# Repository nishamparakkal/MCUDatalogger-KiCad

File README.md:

# MCU Datalogger

## Overview

A microcontroller-based data logger designed in KiCad.

The design uses an ATmega328P microcontroller, DS1337 real-time clock, and external EEPROM memory for time-stamped data storage.

## Features

- ATmega328P-AU microcontroller
- DS1337 Real-Time Clock (RTC)
- Dual 24LC1025 EEPROM memory chips
- External crystal oscillators
- Status indicator LEDs
- I2C communication bus
- Expansion pin headers
- Two-layer PCB design
- ERC and DRC verified
- Manufacturing-ready Gerber files

## Tools Used
- KiCad 10
- Git

## Schematic

## PCB Layout

## 3D View

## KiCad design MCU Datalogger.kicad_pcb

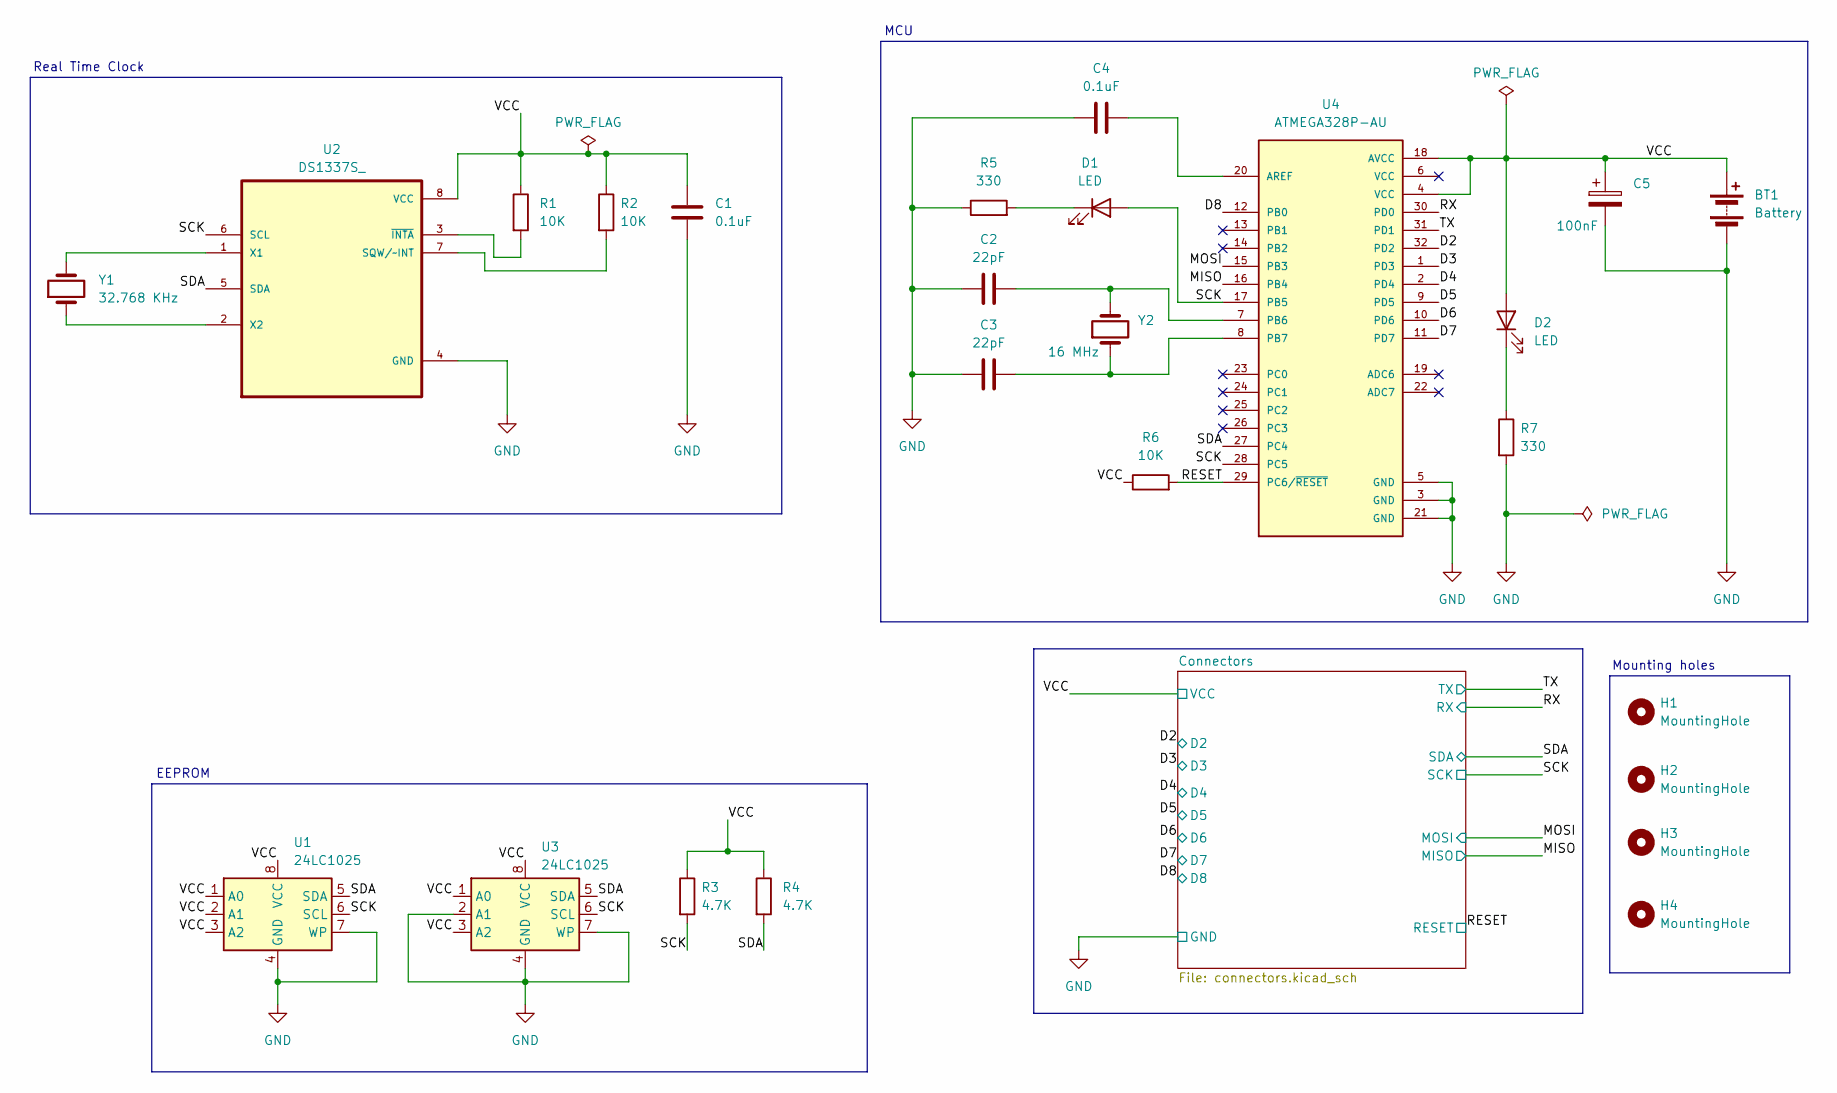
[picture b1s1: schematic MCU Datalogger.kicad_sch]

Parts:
BT1: Battery; PinHeader_1x02_P2.54mm_Vertical
C1, C4: 0.1uF; C_0805_2012Metric
C2, C3: 22pF; C_0805_2012Metric
C5: 100nF; C_0805_2012Metric
D1, D2: LED; LED_0805_2012Metric
H1, H2, H3, H4: MountingHole; MountingHole_2.1mm
R1, R2, R6: 10K; R_0805_2012Metric
R3, R4: 4.7K; R_0805_2012Metric
R5, R7: 330; R_0805_2012Metric
U1, U3: 24LC1025; SOIC-8_5.3x5.3mm_P1.27mm
U2: DS1337S_; SOIC127P600X175-8N
U4: ATMEGA328P-AU; QFP80P900X900X120-32N; PARTREV 8271A
Y1: 32.768 KHz; Crystal_SMD_5032-2Pin_5.0x3.2mm_HandSoldering
Y2: 16 MHz; Crystal_SMD_5032-2Pin_5.0x3.2mm_HandSoldering

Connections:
/D2: U4.32 (PD2); also elsewhere on the board
/D3: U4.1 (PD3); also elsewhere on the board
/D4: U4.2 (PD4); also elsewhere on the board
/D5: U4.9 (PD5); also elsewhere on the board
/D6: U4.10 (PD6); also elsewhere on the board
/D7: U4.11 (PD7); also elsewhere on the board
/D8: U4.12 (PB0); also elsewhere on the board
/MISO: U4.16 (PB4); also elsewhere on the board
/MOSI: U4.15 (PB3); also elsewhere on the board
/RESET: R6.2, U4.29 (PC6/~RESET); also elsewhere on the board
/RX: U4.30 (PD0); also elsewhere on the board
/SCK: D1.2 (A), R3.2, U1.6 (SCL), U2.6 (SCL), U3.6 (SCL), U4.17 (PB5), U4.28 (PC5); also elsewhere on the board
/SDA: R4.2, U1.5 (SDA), U2.5 (SDA), U3.5 (SDA), U4.27 (PC4); also elsewhere on the board
/TX: U4.31 (PD1); also elsewhere on the board
/VCC: BT1.1 (+), C1.1, C5.1, D2.2 (A), R1.1, R2.1, R3.1, R4.1, R6.1, U1.1 (A0), U1.2 (A1), U1.3 (A2), U1.8 (VCC), U2.8 (VCC), U3.1 (A0), U3.3 (A2), U3.8 (VCC), U4.4 (VCC), U4.18 (AVCC); also elsewhere on the board
GND: BT1.2 (-), C1.2, C2.2, C3.1, C4.1, C5.2, R5.1, R7.2, U1.4 (GND), U1.7 (WP), U2.4 (GND), U3.2 (A1), U3.4 (GND), U3.7 (WP), U4.3 (GND), U4.5 (GND), U4.21 (GND); also elsewhere on the board
unnamed: D1.1 (K), R5.2
unnamed: D2.1 (K), R7.1
unnamed: R2.2, U2.7 (SQW/~INT)
unnamed: U2.1 (X1), Y1.2
unnamed: U2.2 (X2), Y1.1
unnamed: R1.2, U2.3 (~INTA)
unnamed: C4.2, U4.20 (AREF)
unnamed: C2.1, U4.7 (PB6), Y2.2
unnamed: C3.2, U4.8 (PB7), Y2.1

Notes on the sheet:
EEPROM
MCU
Real Time Clock
Mounting holes

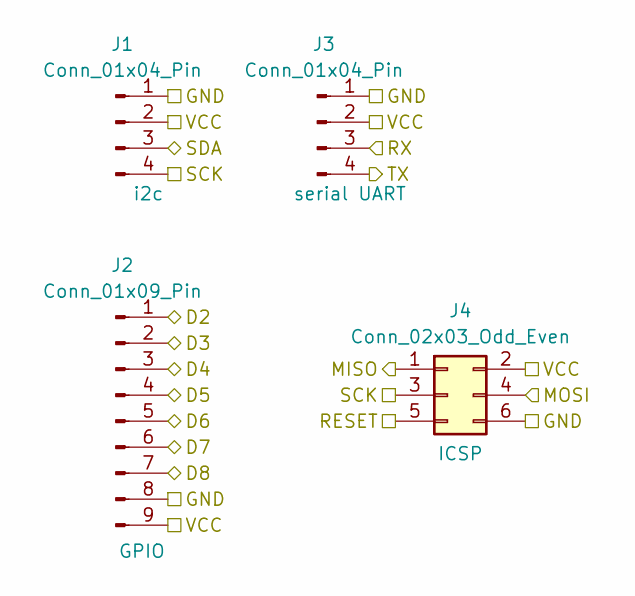
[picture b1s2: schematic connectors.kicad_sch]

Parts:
J1, J3: Conn_01x04_Pin; PinHeader_1x04_P2.54mm_Vertical
J2: Conn_01x09_Pin; PinHeader_1x09_P2.54mm_Vertical
J4: Conn_02x03_Odd_Even; PinHeader_2x03_P2.54mm_Vertical

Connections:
/D2: J2.1; also elsewhere on the board
/D3: J2.2; also elsewhere on the board
/D4: J2.3; also elsewhere on the board
/D5: J2.4; also elsewhere on the board
/D6: J2.5; also elsewhere on the board
/D7: J2.6; also elsewhere on the board
/D8: J2.7; also elsewhere on the board
/MISO: J4.1; also elsewhere on the board
/MOSI: J4.4; also elsewhere on the board
/RESET: J4.5; also elsewhere on the board
/RX: J3.3; also elsewhere on the board
/SCK: J1.4, J4.3; also elsewhere on the board
/SDA: J1.3; also elsewhere on the board
/TX: J3.4; also elsewhere on the board
/VCC: J1.2, J2.9, J3.2, J4.2; also elsewhere on the board
GND: J1.1, J2.8, J3.1, J4.6; also elsewhere on the board

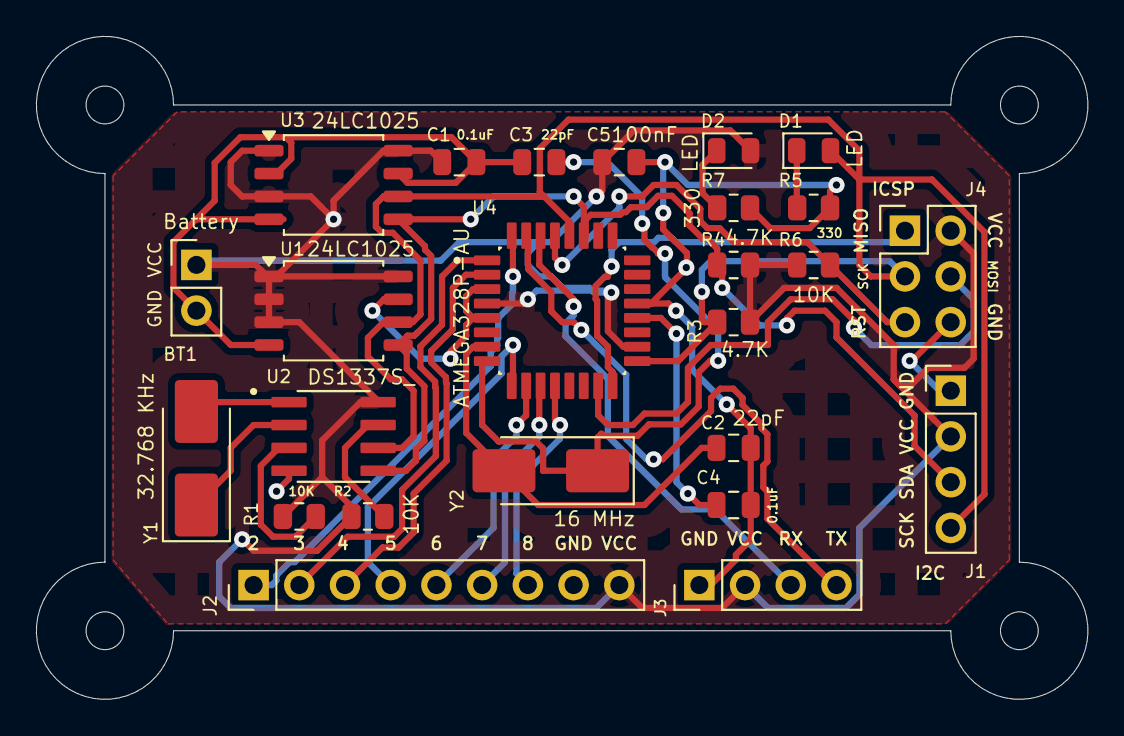
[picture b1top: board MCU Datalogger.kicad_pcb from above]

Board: 2 copper layers, 58.4 x 36.8 mm, 29 parts (0 on the bottom side), 25 nets.

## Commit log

2026-06-24 First commit of a new project.
2026-06-24 setup of eeschea for new project
2026-06-25 have added required schematics to the sheets
2026-06-25 changes the locations of the sympols
2026-06-25 assigned values
2026-06-25 assigned footprints
2026-06-25 wiring on sheet 1 done
2026-06-25 wiring on sheet 2 done
2026-06-25 completed
2026-06-25 2 layer started
2026-06-25 completed placements of footprints
2026-06-25 finished tracks
2026-06-25 finished copper fields
2026-06-25 finished silkscreen
2026-06-25 finished 2 layer
2026-06-25 Create screenshots
